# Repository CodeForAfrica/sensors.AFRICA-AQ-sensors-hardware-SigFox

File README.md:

# sensors.AFRICA SigFox AQ Kits Hardware

## Tools used

* Autodesk Eagle

* Fusion360

## sensors.AFRICA Stack

1. Firmware - https://github.com/CodeForAfrica/sensors.AFRICA-AQ-sensors-software
2. API - https://github.com/CodeForAfricaLabs/sensors.AFRICA-AQ-api
3. Map - https://github.com/CodeForAfrica/sensors.AFRICA-AQ-map-v2

## Documentation

The Documentation is under development.

## License

GNU General Public License v3.0

sensors.AFRICA is a citizen-science focused project by Code for Africa that seeks to address data gaps by providing low cost sensors, which people can use to measure and monitor the quality of the air, water, and environment in their communities. This web app seeks to be the public portal through which most users would discover and explore the data and intiative.

Copyright (C) 2021 Code for Africa

This program is free software: you can redistribute it and/or modify
it under the terms of the GNU General Public License as published by
the Free Software Foundation, either version 3 of the License, or
(at your option) any later version.

This program is distributed in the hope that it will be useful,
but WITHOUT ANY WARRANTY; without even the implied warranty of
MERCHANTABILITY or FITNESS FOR A PARTICULAR PURPOSE. See the
GNU General Public License for more details.

You should have received a copy of the GNU General Public License
along with this program. If not, see <https://www.gnu.org/licenses/>

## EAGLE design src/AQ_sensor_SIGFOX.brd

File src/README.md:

# sensors.AFRICA / SigFox AQ sensors hardware

This folder contains the Eagle design files for the sensors.AFRICA SigFox boards.

### Folders

* **AQ_sensor** The Printed Circuit Board of the AQ kit

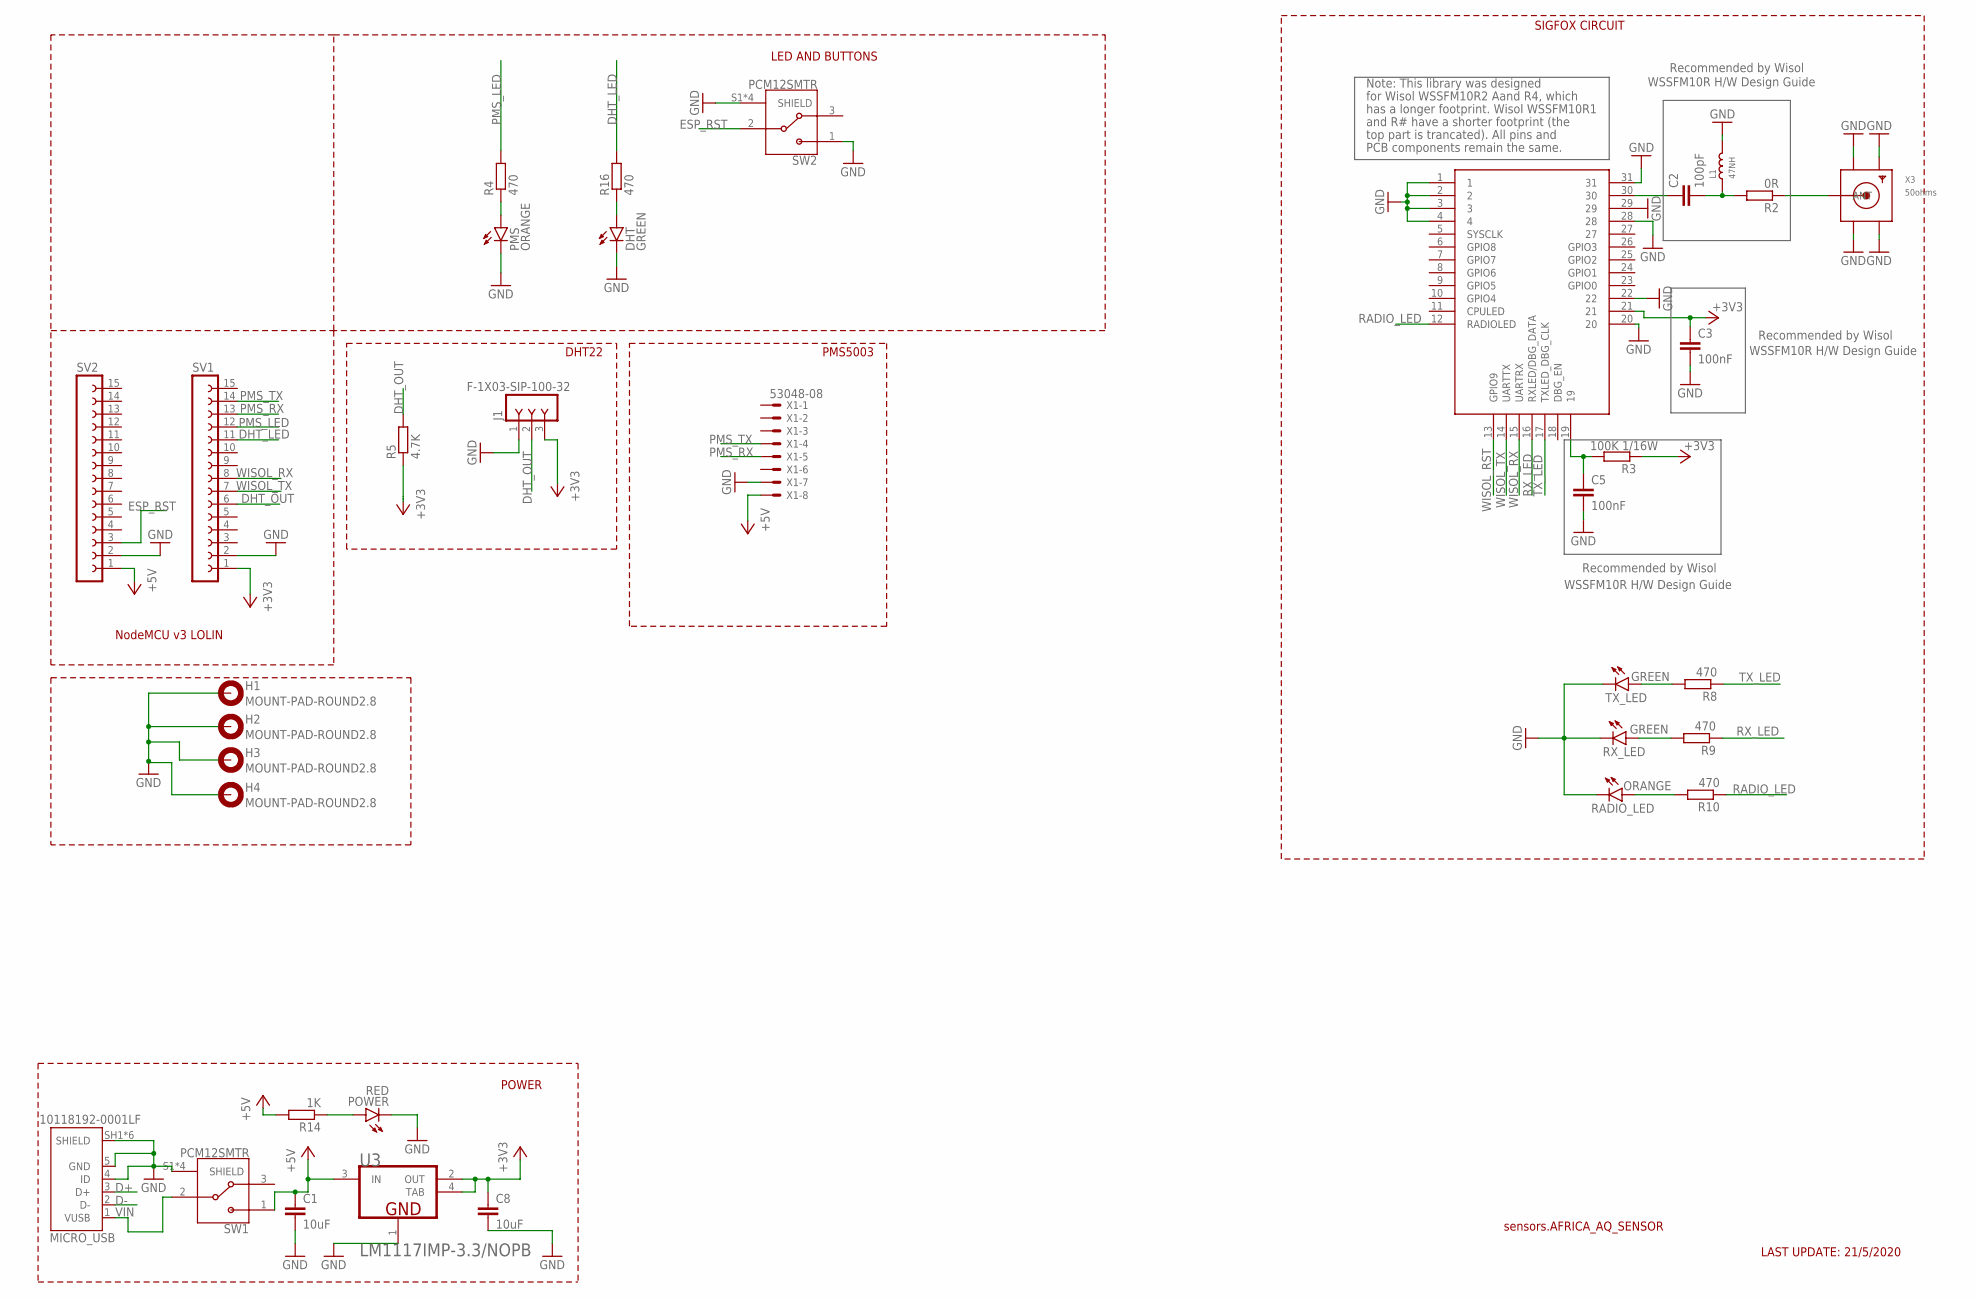
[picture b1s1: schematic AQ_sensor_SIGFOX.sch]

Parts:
C1, C8: 10uF; C0603
C2: 100pF; C0603
C3, C5: 100nF; C0603
DHT: GREEN; CHIP-LED0603
H1, H2, H3, H4: MOUNT-PAD-ROUND2.8; 2,8-PAD
J1: F-1X03-SIP-100-32; SIP-100-03-32
L1: 47NH; L0805
MICRO_USB: 10118192-0001LF; AMPHENOL_10118192-0001LF
PMS: ORANGE; CHIP-LED0603
POWER: RED; CHIP-LED0603
R2: 0R; R0603
R3: 100K 1/16W; R0603
R4, R8, R9, R10, R16: 470; R0603
R5: 4.7K; R0603
R14: 1K; R0603
RADIO_LED: ORANGE; CHIP-LED0603
RX_LED: GREEN; CHIP-LED0603
SV1, SV2: FE15-1; FE15
SW1, SW2: PCM12SMTR; SW_PCM12SMTR
TX_LED: GREEN; CHIP-LED0603
U3: TEXAS_INSTRUMENTS_LM1117IMP-3.3-NOPBTEXAS_INSTRUM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; TEXAS_INSTRUMENTS_LM1117IMP-3.3-NOPB_0
U$1: WSSFM10RWSSFM10R2R4; WSSFM10R
X1: 53048-08
X3: 50ohms; SMA_EDGELAUNCH_UFL

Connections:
+3V3: C3.1, C8.1, J1.3, R3.1, R5.1, SV1.1, U3.2 (OUT), U3.4 (TAB), U$1.21
+5V: C1.1, R14.2, SV2.1, SW1.1, U3.3 (IN), X1.8
D+: MICRO_USB.3 (D+)
D-: MICRO_USB.2 (D-)
DHT_LED: R16.2, SV1.11
DHT_OUT: J1.2, R5.2, SV1.6
ESP_RST: SV2.3, SW2.2
GND: C1.2, C3.2, C5.2, C8.2, DHT.C, H1.B2,8, H2.B2,8, H3.B2,8, H4.B2,8, J1.1, L1.2, MICRO_USB.4 (ID), MICRO_USB.5 (GND), MICRO_USB.SH1 (SHIELD), MICRO_USB.SH2 (SHIELD), MICRO_USB.SH3 (SHIELD), MICRO_USB.SH4 (SHIELD), MICRO_USB.SH5 (SHIELD), MICRO_USB.SH6 (SHIELD), PMS.C, POWER.C, RADIO_LED.C, RX_LED.C, SV1.2, SV2.2, SW1.S1 (SHIELD), SW1.S2 (SHIELD), SW1.S3 (SHIELD), SW1.S4 (SHIELD), SW2.1, SW2.S1 (SHIELD), SW2.S2 (SHIELD), SW2.S3 (SHIELD), SW2.S4 (SHIELD), TX_LED.C, U3.1 (GND), U$1.1, U$1.2, U$1.3, U$1.4, U$1.20, U$1.22, U$1.28, U$1.29, U$1.31, X1.7, X3.GND@1 (GND1), X3.GND@2 (GND2), X3.GND@3 (GND3), X3.GND@4 (GND4)
unnamed: C2.1, U$1.30
unnamed: C2.2, L1.1, R2.2
unnamed: R2.1, X3.P (ANT)
unnamed: PMS.A, R4.1
unnamed: C5.1, R3.2, U$1.19
unnamed: R10.2, RADIO_LED.A
unnamed: R9.2, RX_LED.A
unnamed: R8.2, TX_LED.A
unnamed: POWER.A, R14.1
unnamed: DHT.A, R16.1
PMS_LED: R4.2, SV1.12
PMS_RX: SV1.13, X1.5
PMS_TX: SV1.14, X1.4
RADIO_LED: R10.1, U$1.12 (RADIOLED)
RX_LED: R9.1, U$1.16 (RXLED/DBG_DATA)
TX_LED: R8.1, U$1.17 (TXLED_DBG_CLK)
VIN: MICRO_USB.1 (VUSB), SW1.2
WISOL_RX: SV1.8, U$1.15 (UARTRX)
WISOL_TX: SV1.7, U$1.14 (UARTTX)
WISON_RST: U$1.13 (GPIO9)

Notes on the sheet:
sensors.AFRICA_AQ_SENSOR
LAST UPDATE: 21/5/2020
LED AND BUTTONS
PMS5003
DHT22
NodeMCU v3 LOLIN
POWER
for Wisol WSSFM10R2 Aand R4, which
Note: This library was designed
has a longer footprint. Wisol WSSFM10R1
and R# have a shorter footprint (the
top part is trancated). All pins and
PCB components remain the same.
Recommended by Wisol
WSSFM10R H/W Design Guide
SIGFOX CIRCUIT

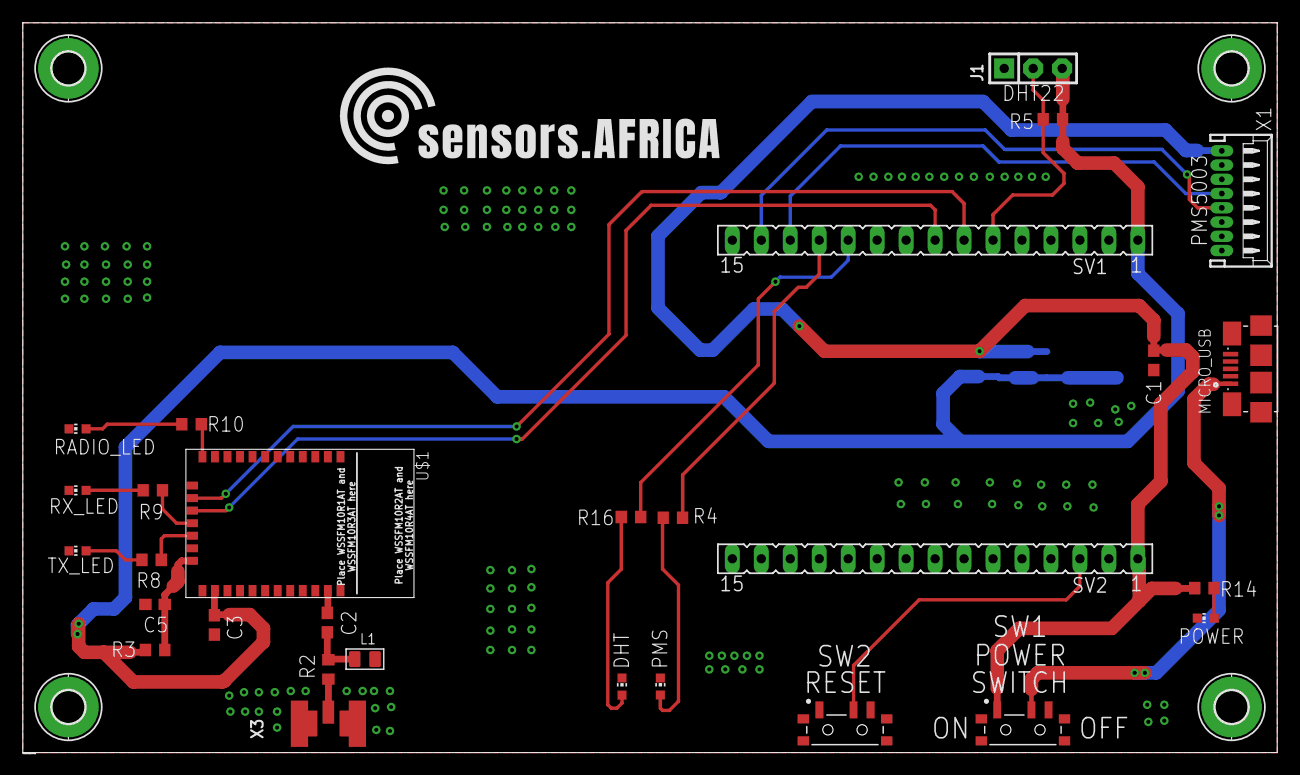
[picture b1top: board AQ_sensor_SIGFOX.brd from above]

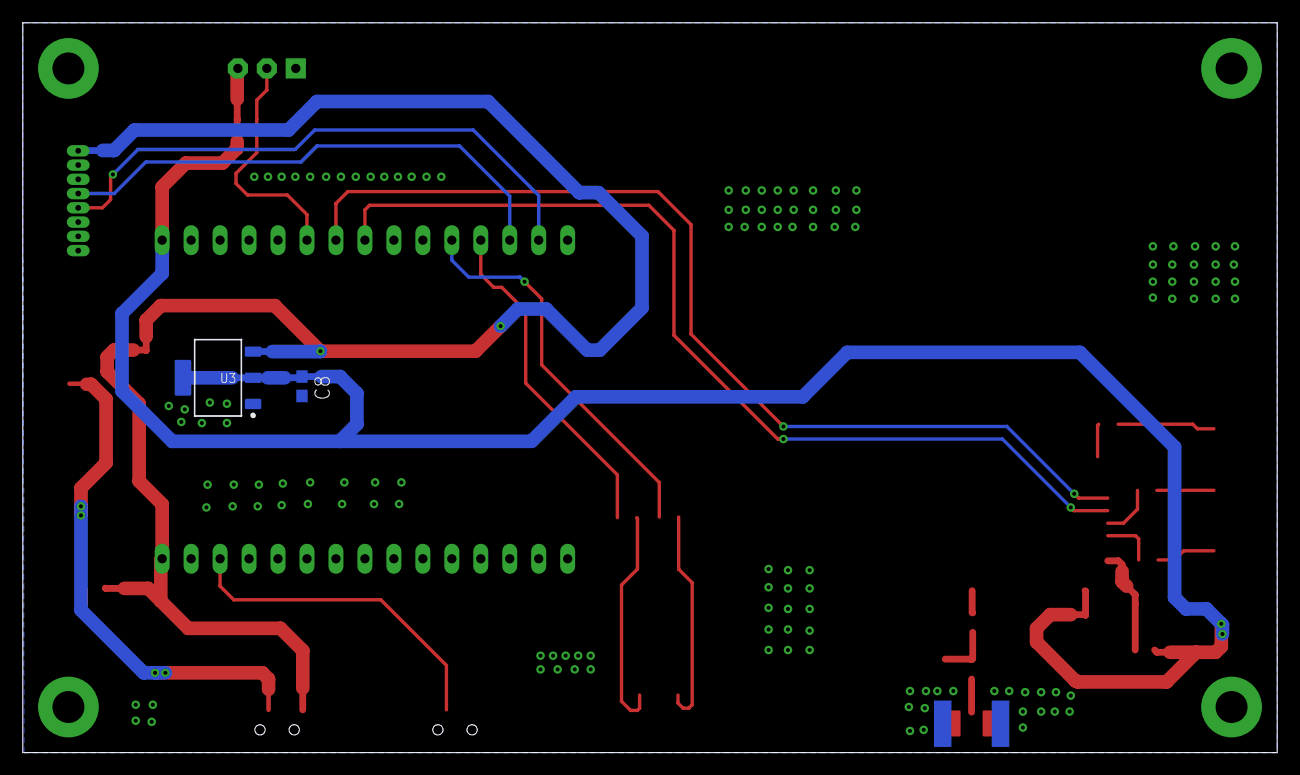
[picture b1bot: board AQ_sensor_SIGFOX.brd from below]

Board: 2 copper layers, 110.0 x 64.0 mm, 35 parts (2 on the bottom side), 25 nets.

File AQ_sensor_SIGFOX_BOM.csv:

"Part";"Value";"Device";"Package";"Description";"AVAILABILITY";"CIIVA_IDS";"CODE__IPC";"CODE__JEDEC";"CODE__JEITA";"COMPONENT_LINK_1_DESCRIPTION";"COMPONENT_LINK_1_URL";"COMP_TYPE";"DESCRIPTION";"FOOTPRINT_VARIANT_NAME_0";"FOOTPRINT_VARIANT_NAME_1";"FOOTPRINT_VARIANT_NAME_2";"HIGH__RELIABILITY";"IMPORTED";"IMPORTED_FROM";"IMPORT_TS";"MF";"MP";"MPN";"OC_FARNELL";"OC_NEWARK";"PACKAGE";"PACKAGE_DESCRIPTION";"PACKAGE_TOP_MARKING";"PIN_COUNT";"POPULARITY";"POWER_WISE";"PREFIX";"PRICE";"RELEASE_DATE";"ROHS";"SPICEPREFIX";"VALUE";"VAULT_GUID";"VAULT_REVISION";
"C1";"10uF";"C-EUC0603";"C0603";"CAPACITOR, European symbol";"";"";"";"";"";"";"";"";"";"";"";"";"";"";"";"";"";"";"";"";"";"";"";"";"";"73";"";"";"";"";"";"C";"";"";"";
"C2";"100pF";"C-EUC0603";"C0603";"CAPACITOR, European symbol";"";"";"";"";"";"";"";"";"";"";"";"";"";"";"";"";"";"";"";"";"";"";"";"";"";"73";"";"";"";"";"";"C";"";"";"";
"C3";"100nF";"C-EUC0603";"C0603";"CAPACITOR, European symbol";"";"";"";"";"";"";"";"";"";"";"";"";"";"";"";"";"";"";"";"";"";"";"";"";"";"73";"";"";"";"";"";"C";"";"";"";
"C5";"100nF";"C-EUC0603";"C0603";"CAPACITOR, European symbol";"";"";"";"";"";"";"";"";"";"";"";"";"";"";"";"";"";"";"";"";"";"";"";"";"";"73";"";"";"";"";"";"C";"";"";"";
"C8";"10uF";"C-EUC0603";"C0603";"CAPACITOR, European symbol";"";"";"";"";"";"";"";"";"";"";"";"";"";"";"";"";"";"";"";"";"";"";"";"";"";"73";"";"";"";"";"";"C";"";"";"";
"DHT";"GREEN";"LEDCHIP-LED0603";"CHIP-LED0603";"LED";"";"";"";"";"";"";"";"";"";"";"";"";"";"";"";"";"";"";"";"";"";"";"";"";"";"26";"";"";"";"";"";"";"";"";"";
"H1";"MOUNT-PAD-ROUND2.8";"MOUNT-PAD-ROUND2.8";"2,8-PAD";"MOUNTING PAD, round";"";"";"";"";"";"";"";"";"";"";"";"";"";"";"";"";"";"";"";"";"";"";"";"";"";"6";"";"";"";"";"";"";"";"";"";
"H2";"MOUNT-PAD-ROUND2.8";"MOUNT-PAD-ROUND2.8";"2,8-PAD";"MOUNTING PAD, round";"";"";"";"";"";"";"";"";"";"";"";"";"";"";"";"";"";"";"";"";"";"";"";"";"";"6";"";"";"";"";"";"";"";"";"";
"H3";"MOUNT-PAD-ROUND2.8";"MOUNT-PAD-ROUND2.8";"2,8-PAD";"MOUNTING PAD, round";"";"";"";"";"";"";"";"";"";"";"";"";"";"";"";"";"";"";"";"";"";"";"";"";"";"6";"";"";"";"";"";"";"";"";"";
"H4";"MOUNT-PAD-ROUND2.8";"MOUNT-PAD-ROUND2.8";"2,8-PAD";"MOUNTING PAD, round";"";"";"";"";"";"";"";"";"";"";"";"";"";"";"";"";"";"";"";"";"";"";"";"";"";"6";"";"";"";"";"";"";"";"";"";
"J1";"F-1X03-SIP-100-32";"F-1X03-SIP-100-32";"SIP-100-03-32";"FEMALE HEADER";"";"";"";"";"";"";"";"";"";"";"";"";"";"";"";"";"";"";"";"";"";"";"";"";"";"";"";"";"";"";"";"";"";"";"";
"L1";"47NH";"SMD-INDUCTOR-2.2UH-20%-1.2A(0805)";"L0805";"303010086";"";"";"";"";"";"";"";"";"";"";"";"";"";"";"";"";"";"";"LQM2MPN2R2MG0";"";"";"";"";"";"";"";"";"";"";"";"";"";"2.2UH-1.2A";"";"";
"MICRO_USB";"10118192-0001LF";"10118192-0001LF";"AMPHENOL_10118192-0001LF";"Single Port 5 Contact Horizontal Right Angle Shielded Micro B USB 2.0 Connector";"Unavailable";"";"";"";"";"";"";"";" USB - micro B USB 2.0 Receptacle Connector 5 Position Surface Mount, Right Angle ";"";"";"";"";"";"";"";"Amphenol ICC";"10118192-0001LF";"";"";"";"None";"";"";"";"";"";"";"None";"";"";"";"";"";"";
"PMS";"ORANGE";"LEDCHIP-LED0603";"CHIP-LED0603";"LED";"";"";"";"";"";"";"";"";"";"";"";"";"";"";"";"";"";"";"";"";"";"";"";"";"";"26";"";"";"";"";"";"";"";"";"";
"POWER";"RED";"LEDCHIP-LED0603";"CHIP-LED0603";"LED";"";"";"";"";"";"";"";"";"";"";"";"";"";"";"";"";"";"";"";"";"";"";"";"";"";"26";"";"";"";"";"";"";"";"";"";
"R2";"0R";"R-EU_R0603";"R0603";"RESISTOR, European symbol";"";"";"";"";"";"";"";"";"";"";"";"";"";"";"";"";"";"";"";"";"";"";"";"";"";"70";"";"";"";"";"";"R";"";"";"";
"R3";"100K 1/16W";"R-EU_R0603";"R0603";"RESISTOR, European symbol";"";"";"";"";"";"";"";"";"";"";"";"";"";"";"";"";"";"";"";"";"";"";"";"";"";"70";"";"";"";"";"";"R";"";"";"";
"R4";"470";"R-EU_R0603";"R0603";"RESISTOR, European symbol";"";"";"";"";"";"";"";"";"";"";"";"";"";"";"";"";"";"";"";"";"";"";"";"";"";"70";"";"";"";"";"";"R";"";"";"";
"R5";"4.7K";"R-EU_R0603";"R0603";"RESISTOR, European symbol";"";"";"";"";"";"";"";"";"";"";"";"";"";"";"";"";"";"";"";"";"";"";"";"";"";"70";"";"";"";"";"";"R";"";"";"";
"R8";"470";"R-EU_R0603";"R0603";"RESISTOR, European symbol";"";"";"";"";"";"";"";"";"";"";"";"";"";"";"";"";"";"";"";"";"";"";"";"";"";"70";"";"";"";"";"";"R";"";"";"";
"R9";"470";"R-EU_R0603";"R0603";"RESISTOR, European symbol";"";"";"";"";"";"";"";"";"";"";"";"";"";"";"";"";"";"";"";"";"";"";"";"";"";"70";"";"";"";"";"";"R";"";"";"";
"R10";"470";"R-EU_R0603";"R0603";"RESISTOR, European symbol";"";"";"";"";"";"";"";"";"";"";"";"";"";"";"";"";"";"";"";"";"";"";"";"";"";"70";"";"";"";"";"";"R";"";"";"";
"R14";"1K";"R-EU_R0603";"R0603";"RESISTOR, European symbol";"";"";"";"";"";"";"";"";"";"";"";"";"";"";"";"";"";"";"";"";"";"";"";"";"";"70";"";"";"";"";"";"R";"";"";"";
"R16";"470";"R-EU_R0603";"R0603";"RESISTOR, European symbol";"";"";"";"";"";"";"";"";"";"";"";"";"";"";"";"";"";"";"";"";"";"";"";"";"";"70";"";"";"";"";"";"R";"";"";"";
"RADIO_LED";"ORANGE";"LEDCHIP-LED0603";"CHIP-LED0603";"LED";"";"";"";"";"";"";"";"";"";"";"";"";"";"";"";"";"";"";"";"";"";"";"";"";"";"26";"";"";"";"";"";"";"";"";"";
"RX_LED";"GREEN";"LEDCHIP-LED0603";"CHIP-LED0603";"LED";"";"";"";"";"";"";"";"";"";"";"";"";"";"";"";"";"";"";"";"";"";"";"";"";"";"26";"";"";"";"";"";"";"";"";"";
"SV1";"";"FE15-1";"FE15";"FEMALE HEADER";"";"";"";"";"";"";"";"";"";"";"";"";"";"";"";"";"";"";"";"unknown";"unknown";"";"";"";"";"2";"";"";"";"";"";"";"";"";"";
"SV2";"";"FE15-1";"FE15";"FEMALE HEADER";"";"";"";"";"";"";"";"";"";"";"";"";"";"";"";"";"";"";"";"unknown";"unknown";"";"";"";"";"2";"";"";"";"";"";"";"";"";"";
"SW1";"PCM12SMTR";"PCM12SMTR";"SW_PCM12SMTR";"Switch Slide ON ON SPDT Side Slide 0.3A 6VDC 10000Cycles Gull Wing SMD T/R";"Unavailable";"";"";"";"";"";"";"";" Slide Switch SPDT Surface Mount, Right Angle ";"";"";"";"";"";"";"";"C&K";"PCM12SMTR";"";"";"";"DO-201 C&amp";"K Components";"";"";"";"";"";"";"None";"";"";"";"";"";
"SW2";"PCM12SMTR";"PCM12SMTR";"SW_PCM12SMTR";"Switch Slide ON ON SPDT Side Slide 0.3A 6VDC 10000Cycles Gull Wing SMD T/R";"Unavailable";"";"";"";"";"";"";"";" Slide Switch SPDT Surface Mount, Right Angle ";"";"";"";"";"";"";"";"C&K";"PCM12SMTR";"";"";"";"DO-201 C&amp";"K Components";"";"";"";"";"";"";"None";"";"";"";"";"";
"TX_LED";"GREEN";"LEDCHIP-LED0603";"CHIP-LED0603";"LED";"";"";"";"";"";"";"";"";"";"";"";"";"";"";"";"";"";"";"";"";"";"";"";"";"";"26";"";"";"";"";"";"";"";"";"";
"U$1";"WSSFM10RWSSFM10R2R4";"WSSFM10RWSSFM10R2R4";"WSSFM10R";"";"";"";"";"";"";"";"";"";"";"";"";"";"";"";"";"";"";"";"";"";"";"";"";"";"";"";"";"";"";"";"";"";"";"";"";
"U3";"TEXAS_INSTRUMENTS_LM1117IMP-3.3-NOPBTEXAS_INSTRUMENTS_LM1117IMP-3.3-NOPB_0_0";"TEXAS_INSTRUMENTS_LM1117IMP-3.3-NOPBTEXAS_INSTRUMENTS_LM1117IMP-3.3-NOPB_0_0";"TEXAS_INSTRUMENTS_LM1117IMP-3.3-NOPB_0";"PM-REG-LM1086-SOT4";"";"19361124";"SOT223-4";"TO-261-AA";"";"Datasheet URL";"http://www.ti.com/general/docs/lit/getliterature.tsp?generic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";"LDO IC";"";"Level C";"Level B";"Level A";"Y";"yes";"vault";"1521845365";"Texas Instruments";"";"LM1117IMP-3.3/NOPB";"";"";"DCY0004A";"Molded SOT-223, 6.50 x 3.56 x 1.6mm Body, 4 Lead, 2.3mm Pitch";"XYTT*N05B";"4";"";"N";"U";"";"1464077430";"Yes";"";"";"7E820BF6-F141-44C1-8A74-392CB201F257";"16019014-2FBF-4157-ADF5-B132B4DC413A";
"X1";"53048-08";"53048-08";"53048-08";"CONNECTOR";"";"";"";"";"";"";"";"";"";"";"";"";"";"";"";"";"WALDOM/MOLEX";"";"53048-0810";"9733094";"38C9913";"";"";"";"";"0";"";"";"";"";"";"";"";"";"";
"X3";"";"SMACONNECTOR_EDGE_UFL";"SMA_EDGELAUNCH_UFL";"SMA Connector";"";"";"";"";"";"";"";"";"";"";"";"";"";"";"";"";"";"";"";"";"";"";"";"";"";"";"";"";"";"";"";"";"";"";"";

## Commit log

2021-08-30 inital commit'
2021-08-30 Added sigfox circuit
2021-09-20 Changed DHT power from 5V to 3v3
2021-09-28 added via stitching
2021-09-28 Added Bill of Materials
2021-09-28 generated manufacturing files
2021-10-04 updated board details to Sigfox
2021-10-04 Added License and documentation
2021-10-04 edited sensor type
2021-10-04 edited board type to sigfox
2021-10-12 sorted DRC
2021-10-12 removed store file
2021-10-18 Added .github directory
2022-01-14 fixed DRC warnings
2022-01-17 updated 3D models
2022-01-17 updated manufacturing files
